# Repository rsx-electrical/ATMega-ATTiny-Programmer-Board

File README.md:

# ATMega ATTiny Programmer Board
UofT RSX's ATMega/ATTiny Programmer Board KiCad PCB designs for programming standalone ATMega328[tbd] and ATTiny[tbd] microcontrollers. Uses Arduino as programmer. By programming the microcontroller directly, custom boards can be smaller and cheaper.

## To-do
- 

## Repository Structure 
```
Programmer-Board/
├── ATMega/
│   └── ...
│
├── ATTiny/
│   └── ...
│
├── Programmer Board/
│   └── ...
│
├── guide.txt
└── README.md
```
## History/Patch Notes

### v1.0 - TBD
- Final Design Version 1

### v0.2 - TBD
- 

### v0.1 - Init
- General Project Struct Formed

## Materials
- Arduino Header
- Electrolytic Capacitor 10uF
- Decoupling Capacitors 100nF
- Resistor [1 - 10kΩ]
- ATMega328[tbd] or ATTiny[tbd] Socket

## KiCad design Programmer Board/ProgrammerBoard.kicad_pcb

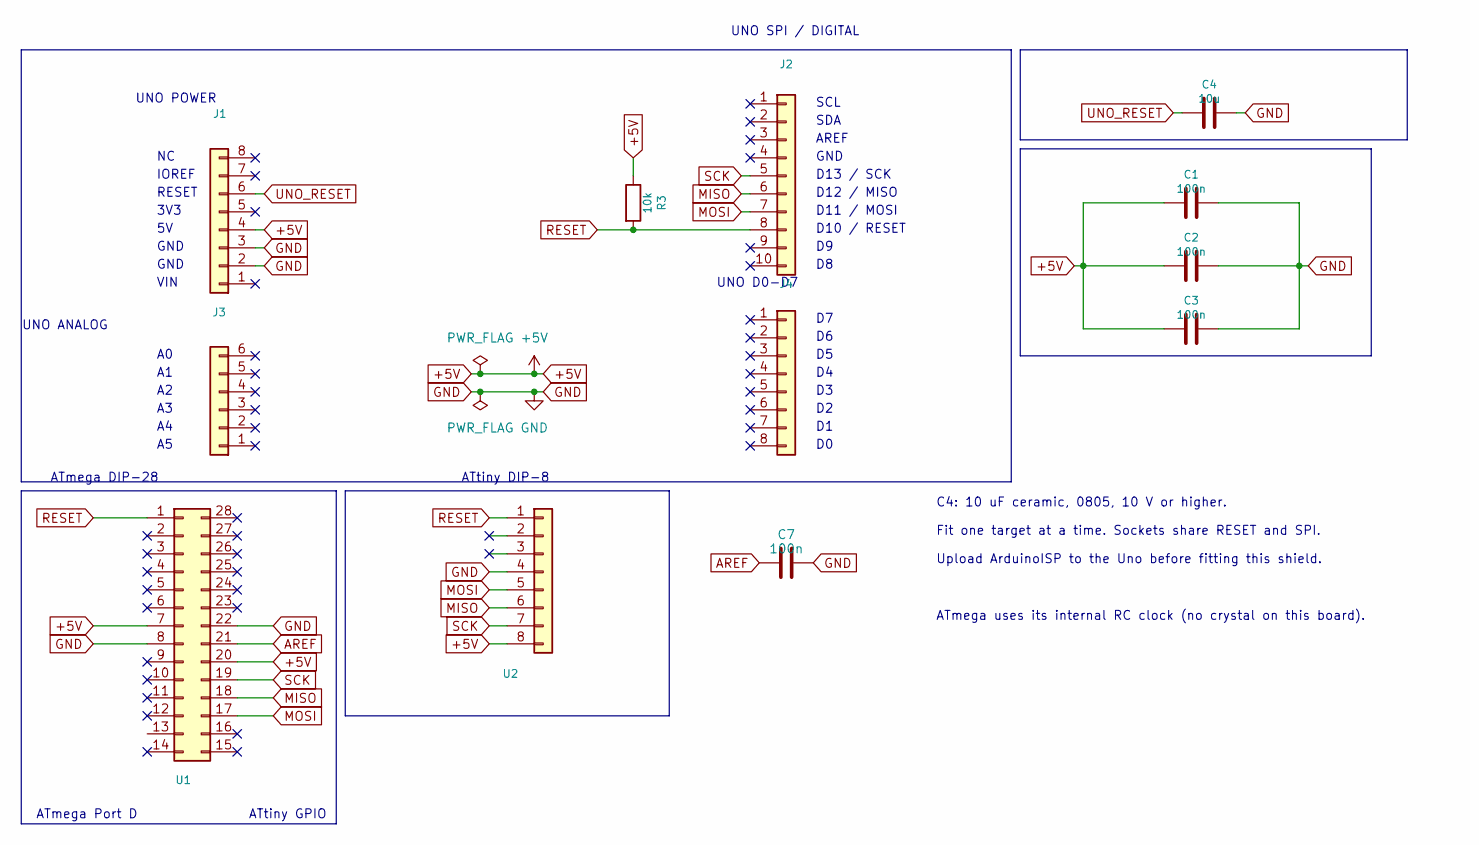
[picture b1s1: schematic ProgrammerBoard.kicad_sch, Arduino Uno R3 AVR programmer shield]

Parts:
C1, C2, C3, C7: 100n; C_0603_1608Metric; MPN C0603C104K5RACTU
C4: 10u; C_0805_2012Metric; MPN GRM21BR61H106KE43L
J1: UNO POWER; PinHeader_1x08_P2.54mm_Vertical; MPN PH1-08-UA
J2: UNO DIGITAL 8–13; PinHeader_1x10_P2.54mm_Vertical; MPN PH1-10-UA
J3: UNO ANALOG; PinHeader_1x06_P2.54mm_Vertical; MPN PH1-06-UA
J4: UNO DIGITAL 0–7; PinHeader_1x08_P2.54mm_Vertical; MPN PH1-08-UA
R3: 10k; R_0603_1608Metric; MPN RMCF0603JT10K0
U1: ATmega328(P) DIP-28; DIP-28_W7.62mm_Socket; MPN ED281DT
U2: ATtiny85 DIP-8; DIP-8_W7.62mm_Socket; MPN 1-2199298-2

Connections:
+5V: C1.1, C2.1, C3.1, J1.4, R3.1, U1.7, U1.20, U2.8
AREF: C7.1, U1.21
GND: C1.2, C2.2, C3.2, C4.1, C7.2, J1.2, J1.3, U1.8, U1.22, U2.4
MISO: J2.6, U1.18, U2.6
MOSI: J2.7, U1.17, U2.5
RESET: J2.8, R3.2, U1.1, U2.1
SCK: J2.5, U1.19, U2.7
UNO_RESET: C4.2, J1.6

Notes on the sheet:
3V3
UNO POWER
ATtiny GPIO
ATmega DIP-28
ATmega uses its internal RC clock (no crystal on this board).
C4: 10 uF ceramic, 0805, 10 V or higher.
GND
UNO ANALOG
SDA
Upload ArduinoISP to the Uno before fitting this shield.
AREF
VIN
D10 / RESET
SCL
D13 / SCK
IOREF
Fit one target at a time. Sockets share RESET and SPI.
UNO D0-D7
ATmega Port D
ATtiny DIP-8
D12 / MISO
UNO SPI / DIGITAL
RESET
D11 / MOSI

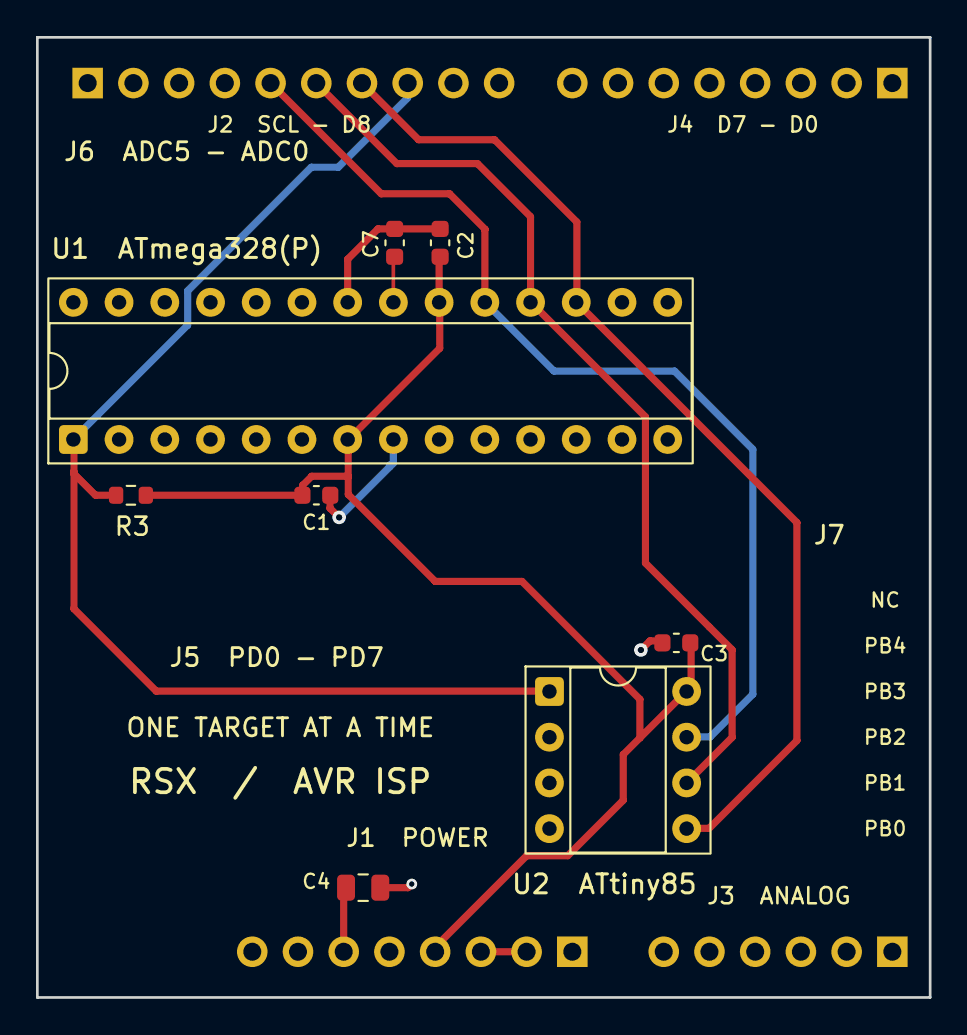
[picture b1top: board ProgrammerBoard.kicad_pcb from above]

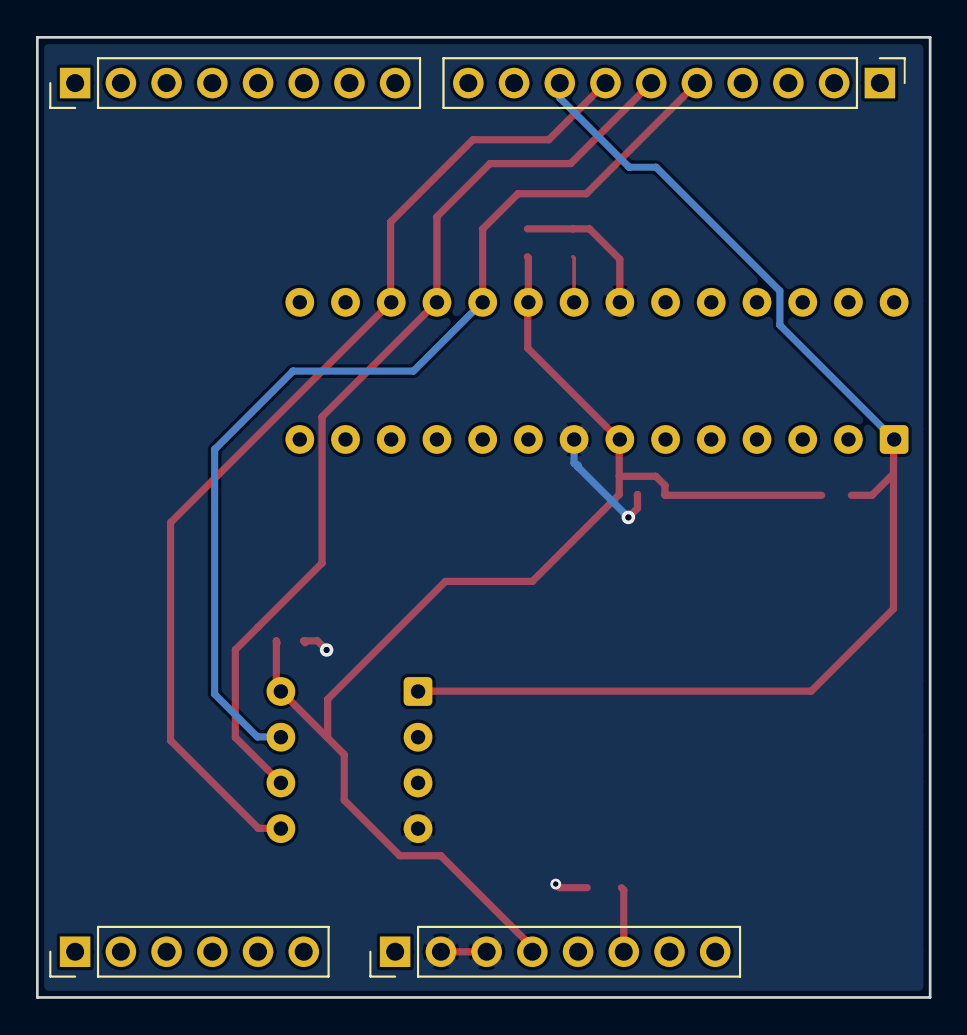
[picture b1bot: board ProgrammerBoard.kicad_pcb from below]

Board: 2 copper layers, 49.6 x 53.3 mm, 12 parts (4 on the bottom side), 8 nets.

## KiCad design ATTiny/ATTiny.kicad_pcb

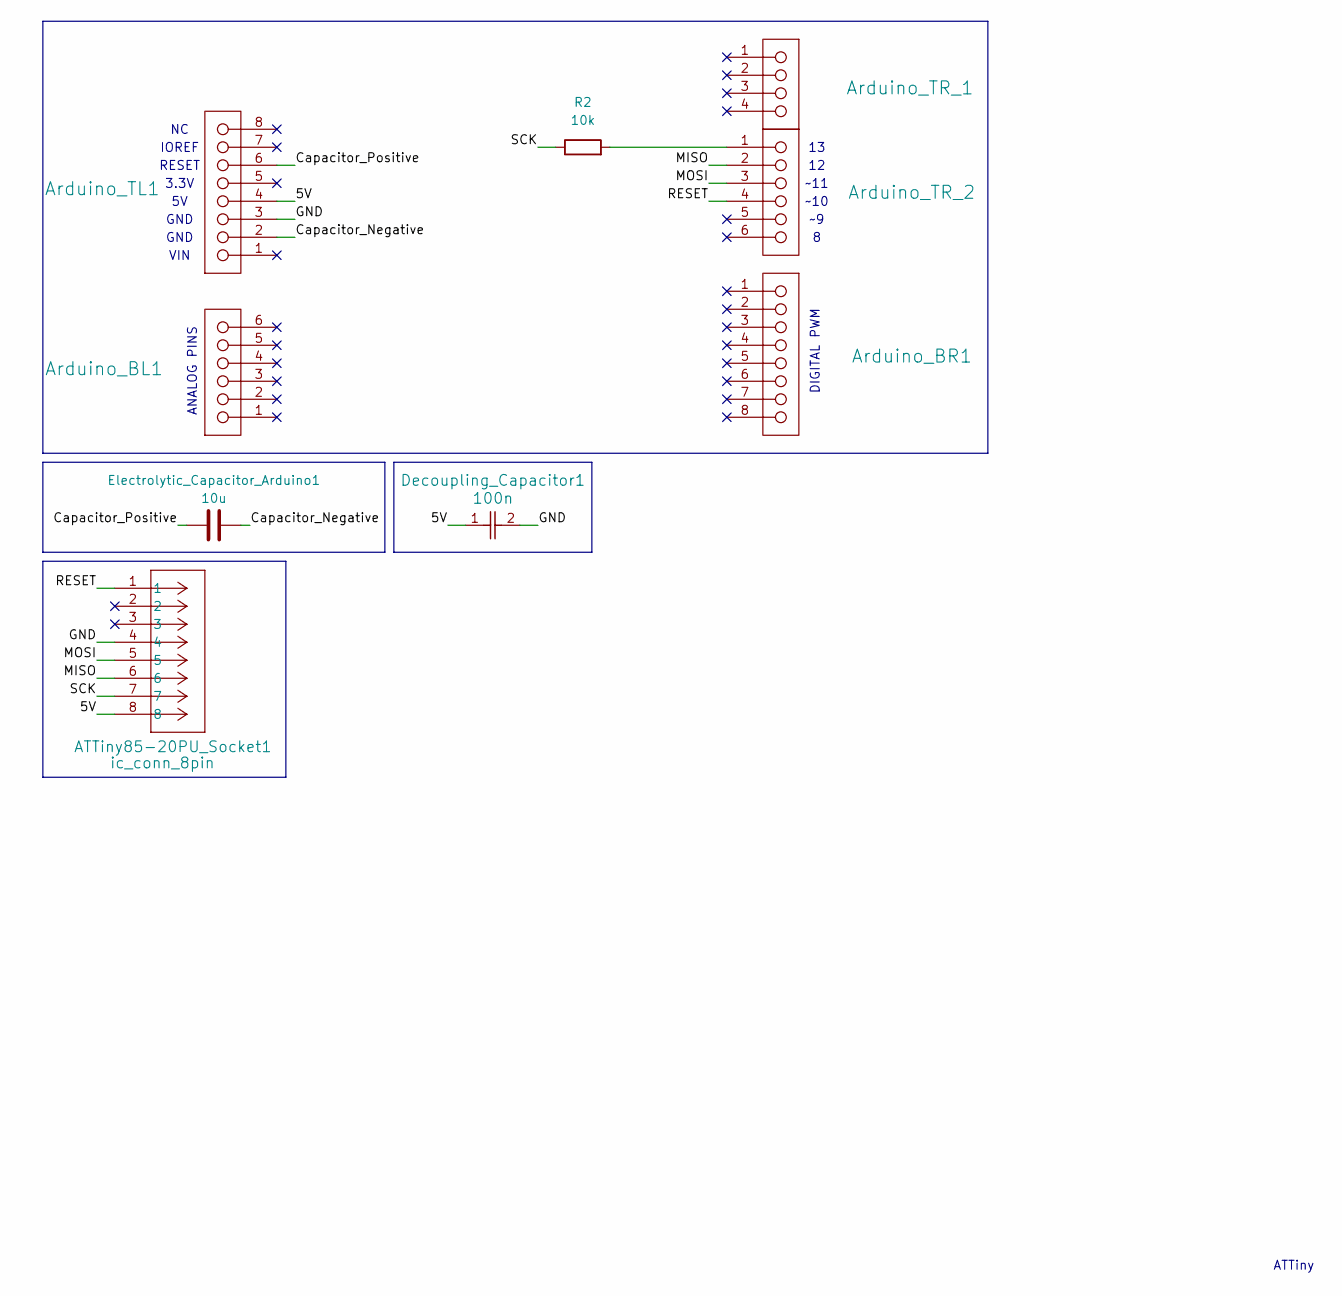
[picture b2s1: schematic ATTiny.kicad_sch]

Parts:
ATTiny85-20PU_Socket1: ic_conn_8pin; CONN8_1-2199298-2_TEC
Arduino_BL1: header_1x6_arduino; PinHeader_1x06_P2.54mm_Vertical; Working Voltage 250V; Withstanding Voltage 500V; Manufacturer Part Number 61000613321
Arduino_BR1: header_1x8_arduino; PinHeader_1x08_P2.54mm_Vertical; Working Voltage 250V; Withstanding Voltage 500V; Manufacturer Part Number 61000813321
Arduino_TL1: header_1x8_arduino; PinHeader_1x08_P2.54mm_Vertical; Working Voltage 250V; Withstanding Voltage 500V; Manufacturer Part Number 61000813321
Arduino_TR_1: header_1x4_arduino; PinHeader_1x04_P2.54mm_Vertical; Working Voltage 250V; Withstanding Voltage 500V; Manufacturer Part Number 61000411921
Arduino_TR_2: header_1x6_arduino; PinHeader_1x06_P2.54mm_Vertical; Working Voltage 250V; Withstanding Voltage 500V; Manufacturer Part Number 61000613321
Decoupling_Capacitor1: 100n; C_0603_1608Metric; MPN C0603C104K5RACTU
Electrolytic_Capacitor_Arduino1: 10u; C_0805_2012Metric; MPN GRM21BR61H106KE43L
R2: 10k; R_0603_1608Metric; MPN RMCF0603JT10K0

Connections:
/5V: ATTiny85-20PU_Socket1.8, Arduino_TL1.4, Decoupling_Capacitor1.1
/Capacitor_Negative: Arduino_TL1.2, Electrolytic_Capacitor_Arduino1.1
/Capacitor_Positive: Arduino_TL1.6, Electrolytic_Capacitor_Arduino1.2
/GND: ATTiny85-20PU_Socket1.4, Arduino_TL1.3, Decoupling_Capacitor1.2
/MISO: ATTiny85-20PU_Socket1.6, Arduino_TR_2.2
/MOSI: ATTiny85-20PU_Socket1.5, Arduino_TR_2.3
/RESET: ATTiny85-20PU_Socket1.1, Arduino_TR_2.4
/SCK: ATTiny85-20PU_Socket1.7, R2.1
unnamed: Arduino_TR_2.1, R2.2

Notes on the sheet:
GND
~10
IOREF
DIGITAL PWM
ANALOG PINS
ATTiny
RESET
3.3V
VIN
~11

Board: 2 copper layers, 9 parts (0 on the bottom side), 9 nets, no tracks yet.

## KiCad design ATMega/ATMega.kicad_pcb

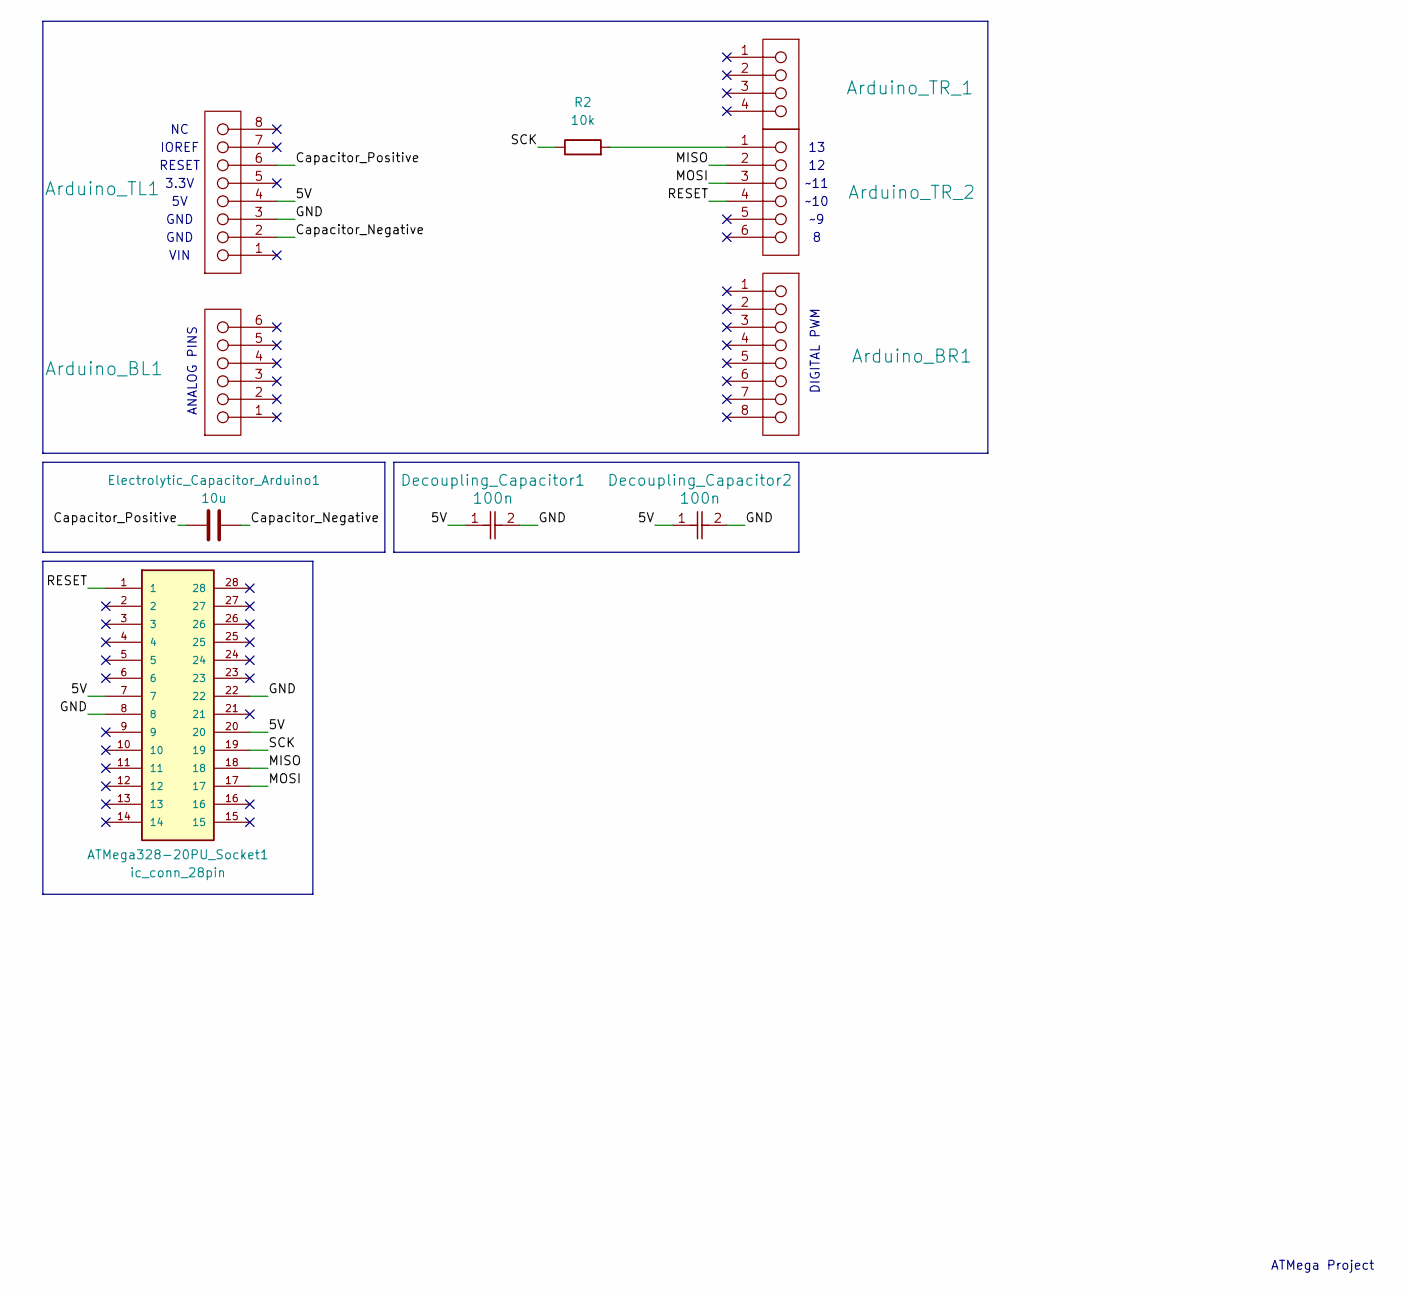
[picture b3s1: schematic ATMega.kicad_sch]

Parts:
ATMega328-20PU_Socket1: ic_conn_28pin; OST_ED281DT; PARTREV D
Arduino_BL1: header_1x6_arduino; PinHeader_1x06_P2.54mm_Vertical; Working Voltage 250V; Withstanding Voltage 500V; Manufacturer Part Number 61000613321
Arduino_BR1: header_1x8_arduino; PinHeader_1x08_P2.54mm_Vertical; Working Voltage 250V; Withstanding Voltage 500V; Manufacturer Part Number 61000813321
Arduino_TL1: header_1x8_arduino; PinHeader_1x08_P2.54mm_Vertical; Working Voltage 250V; Withstanding Voltage 500V; Manufacturer Part Number 61000813321
Arduino_TR_1: header_1x4_arduino; PinHeader_1x04_P2.54mm_Vertical; Working Voltage 250V; Withstanding Voltage 500V; Manufacturer Part Number 61000411921
Arduino_TR_2: header_1x6_arduino; PinHeader_1x06_P2.54mm_Vertical; Working Voltage 250V; Withstanding Voltage 500V; Manufacturer Part Number 61000613321
Decoupling_Capacitor1, Decoupling_Capacitor2: 100n; C_0603_1608Metric; MPN C0603C104K5RACTU
Electrolytic_Capacitor_Arduino1: 10u; C_0805_2012Metric; MPN GRM21BR61H106KE43L
R2: 10k; R_0603_1608Metric; MPN RMCF0603JT10K0

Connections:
/5V: ATMega328-20PU_Socket1.7, ATMega328-20PU_Socket1.20, Arduino_TL1.4, Decoupling_Capacitor1.1, Decoupling_Capacitor2.1
/Capacitor_Negative: Arduino_TL1.2, Electrolytic_Capacitor_Arduino1.1
/Capacitor_Positive: Arduino_TL1.6, Electrolytic_Capacitor_Arduino1.2
/GND: ATMega328-20PU_Socket1.8, ATMega328-20PU_Socket1.22, Arduino_TL1.3, Decoupling_Capacitor1.2, Decoupling_Capacitor2.2
/MISO: ATMega328-20PU_Socket1.18, Arduino_TR_2.2
/MOSI: ATMega328-20PU_Socket1.17, Arduino_TR_2.3
/RESET: ATMega328-20PU_Socket1.1, Arduino_TR_2.4
/SCK: ATMega328-20PU_Socket1.19, R2.1
unnamed: Arduino_TR_2.1, R2.2

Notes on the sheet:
ATMega Project
IOREF
ANALOG PINS
RESET
~10
GND
DIGITAL PWM
~11
3.3V
VIN

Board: 2 copper layers, 10 parts (0 on the bottom side), 9 nets, no tracks yet.
